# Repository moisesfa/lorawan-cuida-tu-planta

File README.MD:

# LoRaWAN Cuida Tu Planta

Pretendo desarrollar un nodo LoRaWAN para monitorizar las condiciones ambientales en las que crece una planta.

El cerebro será la placa de desarrollo [CubeCell](https://heltec.org/project/htcc-ab01/) del fabricante [Heltec Automation](https://heltec.org/). La placa a día de hoy (Septiembre de 20022), no se recomienda para diseños nuevos y le han puesto la etiqueta Phaseout. El fabricante recomienda una CubeCell-Dev-Board (V2) de la que todavía no hay documentación. Esto carece de importancia en este proyecto que pretende ser meramente educativo. También, pueden ser interesantes las modificaciones a la nueva versión en un futuro.
En Octubre de 2022 ya hay documentación de la versión 2 de la [CubeCell-Dev-Board](https://heltec.org/project/htcc-ab01-v2/). A falta de pruebas, parece que va a ser compatible con la placa diseñada.  

Se ha diseñado un circuito impreso para alimentar el circuito con una batería 18650 y poder conectar fácilmente los sensores i2c a usar. Vea la documentación [aquí](/hardware/README.md)

Temperatura, Humedad, Presión Atmosférica se obtendran con el sensor [BME280](https://www.luisllamas.es/sensor-ambiental-arduino-bme280/)

Para el nivel de luz, un sensor digital [BH1750](https://www.luisllamas.es/medir-cantidad-de-luxes-con-arduino-y-el-luxometro-bh1750/)

El sensor de humedad del suelo será un [higrómetro capacitivo](https://www.luisllamas.es/sensor-de-humedad-del-suelo-capacitivo-y-arduino/) para el que necesitaremos un conversor analógico digital (ADC) como el [ADS1115](https://www.luisllamas.es/entrada-analogica-adc-de-16-bits-con-arduino-y-ads1115/) ya que la CubeCell no dispone de entradas analógicas libres. Esto también nos dará la posibilidad de conectar hasta 4 sensores de humedad de suelo. 

<div style="text-align: center;">

</div>

## Fases del proyecto 

- Lectura de los sensores con el puerto serie.
    - [BME280](/software/02_inicio_bme280/README.md)
    - [BH1750](/software/03_inicio_bh1750/README.md)
    - [Conversor analógico-digital para humedad del suelo](/software/04_inicio_ads1115/README.md)
    - [Lectura de todos los sensores](/software/05_sensores_todos/README.md)

- Envio de datos LoRaWAN
    - [Inicio con LoRaWAN](/software/06_inicio_lorawan/README.md)
    - [Lectura de los sensores a LoRaWAN](/software/07_sensores_lorawan/README.md)

## Resultado final

Para proteger el sensor de humedad del suelo he seguido estas [instrucciones](https://www.instructables.com/Waterproofing-a-Capacitance-Soil-Moisture-Sensor/)

El sensor de luminosidad se ha usado en este [formato de bola](https://a.aliexpress.com/_ExYB4vB) para una mejor colocación.

## Análisis de consumo

He analizado el consumo con el [Power-Profiler-Kit-2](https://www.nordicsemi.com/Products/Development-hardware/Power-Profiler-Kit-2) y dejo aquí los resultados.

<div style="text-align: center;">

</div>

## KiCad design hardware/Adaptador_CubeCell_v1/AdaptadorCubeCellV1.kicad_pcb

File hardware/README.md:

# Documentación sobre circuito impreso adaptador

[Esquema](./Adaptador_CubeCell_v1/docs/Adaptador_CubeCell_v1_sch.pdf) y [PCB](./Adaptador_CubeCell_v1/docs/Adaptador_CubeCell_v1_pcb.pdf) diseñados con [Kicad](https://www.kicad.org/)

Se ha diseñado para que se pueda alojar en esta [caja](https://a.aliexpress.com/_dWu4tJt)

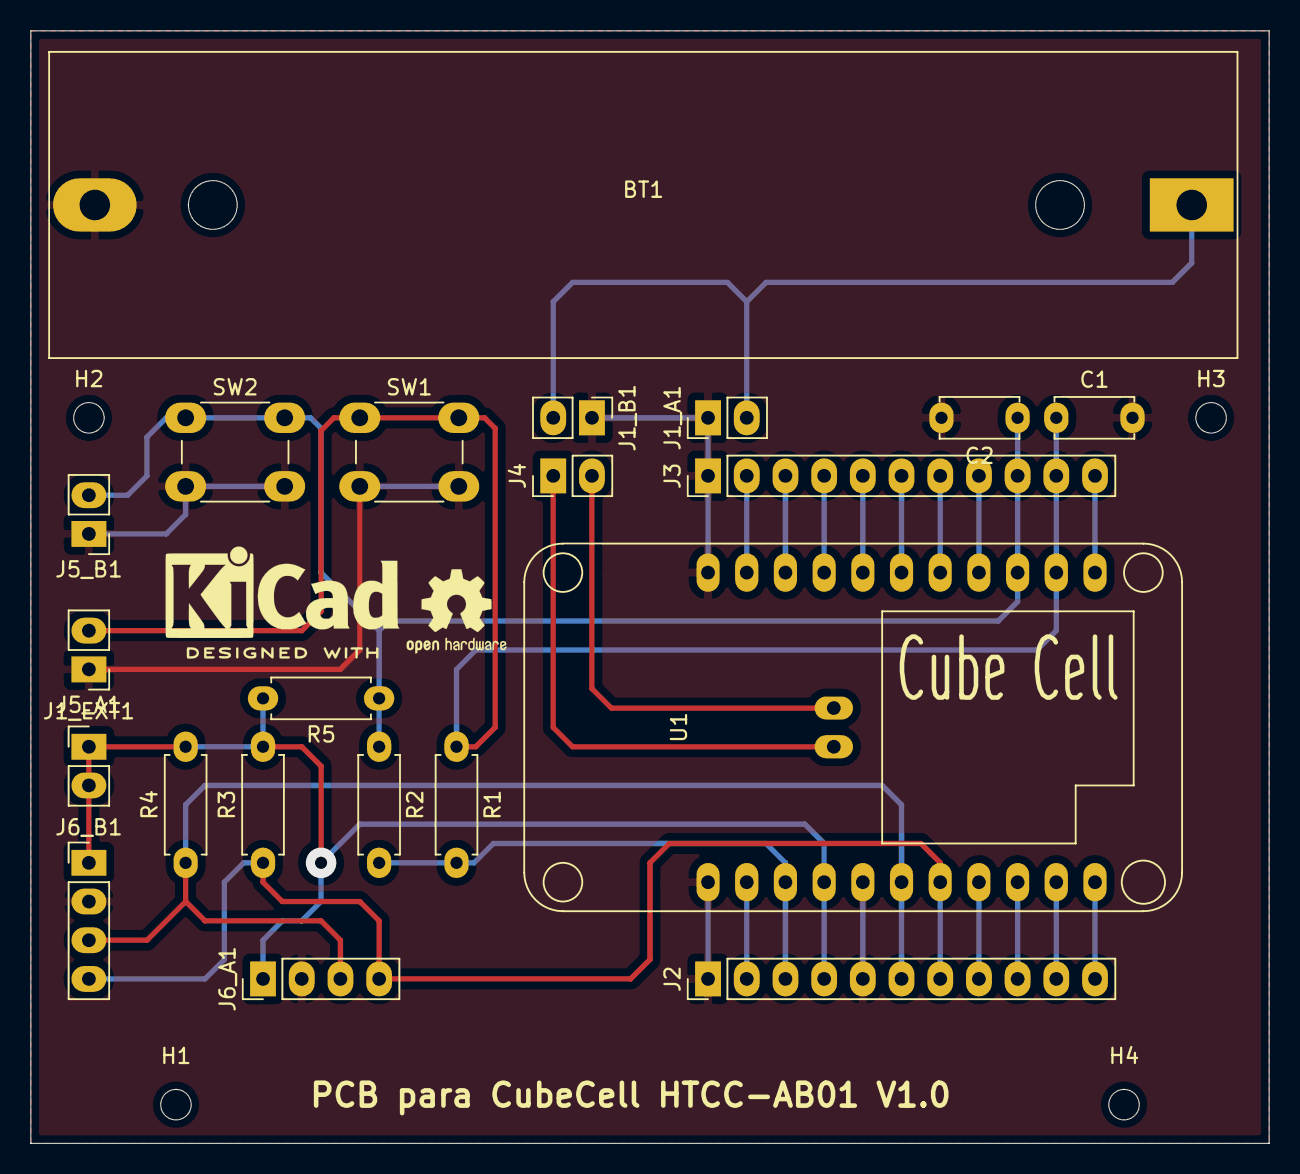
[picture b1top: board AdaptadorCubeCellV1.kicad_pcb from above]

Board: 2 copper layers, 81.3 x 73.0 mm, 25 parts (0 on the bottom side), 23 nets.

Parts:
BT1: Battery_Cell; BatteryHolder_MPD_BH-18650-PC2
C1, C2: 1uF; C_Disc_D5.0mm_W2.5mm_P5.00mm
H1, H2, H3, H4: MountingHole_2mm
J1_A1: BAT_1; PinHeader_1x02_P2.54mm_Vertical_custom
J1_B1: BAT_2; PinHeader_1x02_P2.54mm_Vertical_custom
J1_EXT1: EXT_1; PinHeader_1x02_P2.54mm_Vertical_custom
J2: CONECTOR_A; PinHeader_1x11_P2.54mm_Vertical
J3: CONECTOR_B; PinHeader_1x11_P2.54mm_Vertical
J4: CONECTOR_C; PinHeader_1x02_P2.54mm_Vertical_custom
J5_A1: INT1; PinHeader_1x02_P2.54mm_Vertical_custom
J5_B1: INT2; PinHeader_1x02_P2.54mm_Vertical_custom
J6_A1: I2C_A; PinHeader_1x04_P2.54mm_Vertical
J6_B1: I2C_B; PinHeader_1x04_P2.54mm_Vertical
R1, R2, R3, R4: 10K; R_Axial_DIN0207_L6.3mm_D2.5mm_P7.62mm_Horizontal
R5: 4K7; R_Axial_DIN0207_L6.3mm_D2.5mm_P7.62mm_Horizontal
SW1, SW2: SW_Push; SW_PUSH_6mm_H5mm
U1: CUBECELL_HTCC-AB01; CubeCell_HTCC-AB01

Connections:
+3V3: J2.3, R1.2, R2.2, U1.3
+BATT: BT1.1, J1_A1.2, J1_B1.2
/GPIO1: C1.1, J3.10, J5_A1.2, R1.1, SW1.1, U1.13
/GPIO2: C2.1, J3.9, J5_B1.2, R2.1, R5.1, SW2.1, U1.14
/SCL: J2.6, J6_A1.3, J6_B1.3, R4.1, U1.6
/SDA: J2.7, J6_A1.4, J6_B1.4, R3.1, U1.7
/VEXT: J1_EXT1.1, J1_EXT1.2, J2.4, J6_A1.1, J6_B1.1, R3.2, R4.2, R5.2, U1.4
GND: BT1.2, C1.2, C2.2, J1_A1.1, J1_B1.1, J2.1, J2.5, J3.1, J5_A1.1, J5_B1.1, J6_A1.2, J6_B1.2, SW1.2, SW2.2, U1.1, U1.5, U1.22
unnamed: J2.2, U1.2
unnamed: J2.8, U1.8
unnamed: J2.9, U1.9
unnamed: J2.10, U1.10
unnamed: J2.11, U1.11
unnamed: J3.2, U1.21
unnamed: J3.3, U1.20
unnamed: J3.4, U1.19
unnamed: J3.5, U1.18
unnamed: J3.6, U1.17
unnamed: J3.7, U1.16
unnamed: J3.8, U1.15
unnamed: J3.11, U1.12
unnamed: J4.1, U1.23
unnamed: J4.2, U1.24

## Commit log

2022-09-28 primer commit
2022-09-29 helloWorld commit
2022-10-02 añado la lectura sensor BME280
2022-10-02 creando licencia
2022-10-06 añado sensor BH1750 commit
2022-10-08 añado lectura con ads1115 commit
2022-10-09 añado doc cubecel v2 commit
2022-10-09 añado lectura todos commit
2022-10-10 añado inicio lorawan commit
2022-10-12 añado senores lorawan commit
2022-10-12 añado grafico
2022-10-14 cambio de imagenes commit
2022-10-20 mejoras en la documentacion commit
2022-10-23 mejoras en sensor de humedad commit
2022-10-23 mejoras en sensor de humedad lorawan commit
2022-10-24 mejoras en docs commit
2022-11-06 resultado final commit
2022-12-17 Añado mejoras
2023-01-20 Solucion bug ads1115
2023-02-01 Corrección de porcentajes humedad
2023-03-01 solución a error al iniciar
